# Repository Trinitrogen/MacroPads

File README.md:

# MacroPads
Repository for various Macropads

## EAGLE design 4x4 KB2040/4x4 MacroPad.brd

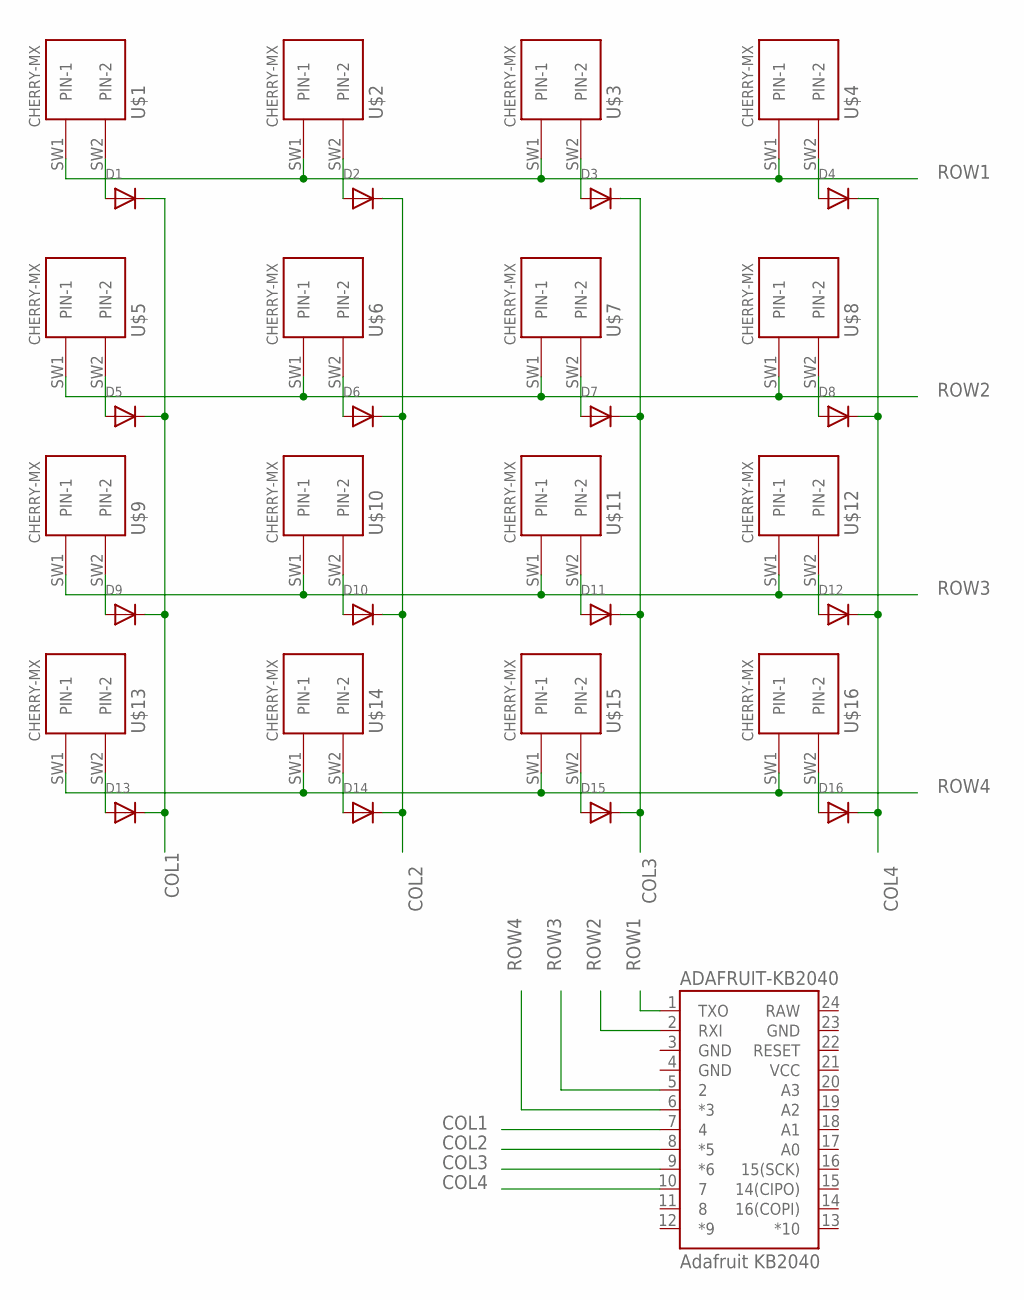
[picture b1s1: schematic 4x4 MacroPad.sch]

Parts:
ADAFRUIT-KB2040: Adafruit KB2040; SPARKFUN_PRO_MICRO
D1, D2, D3, D4, D5, D6, D7, D8, D9, D10, D11, D12, D13, D14, D15, D16: DIODESOD-123; SOD-123
U$1, U$2, U$3, U$4, U$5, U$6, U$7, U$8, U$9, U$10, U$11, U$12, U$13, U$14, U$15, U$16: CHERRY-MX

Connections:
C1: D1.A, U$1.SW2 (PIN-2)
C2: D2.A, U$2.SW2 (PIN-2)
C3: D3.A, U$3.SW2 (PIN-2)
C4: D4.A, U$4.SW2 (PIN-2)
COL1: ADAFRUIT-KB2040.7 (4), D1.C, D5.C, D9.C, D13.C
COL2: ADAFRUIT-KB2040.8 (*5), D2.C, D6.C, D10.C, D14.C
COL3: ADAFRUIT-KB2040.9 (*6), D3.C, D7.C, D11.C, D15.C
COL4: ADAFRUIT-KB2040.10 (7), D4.C, D8.C, D12.C, D16.C
GND: ADAFRUIT-KB2040.3 (GND), ADAFRUIT-KB2040.4 (GND), ADAFRUIT-KB2040.23 (GND)
unnamed: D5.A, U$5.SW2 (PIN-2)
unnamed: D6.A, U$6.SW2 (PIN-2)
unnamed: D7.A, U$7.SW2 (PIN-2)
unnamed: D8.A, U$8.SW2 (PIN-2)
unnamed: D9.A, U$9.SW2 (PIN-2)
unnamed: D10.A, U$10.SW2 (PIN-2)
unnamed: D11.A, U$11.SW2 (PIN-2)
unnamed: D12.A, U$12.SW2 (PIN-2)
unnamed: D13.A, U$13.SW2 (PIN-2)
unnamed: D14.A, U$14.SW2 (PIN-2)
unnamed: D15.A, U$15.SW2 (PIN-2)
unnamed: D16.A, U$16.SW2 (PIN-2)
RAW: ADAFRUIT-KB2040.24 (RAW)
ROW1: ADAFRUIT-KB2040.1 (TXO), U$1.SW1 (PIN-1), U$2.SW1 (PIN-1), U$3.SW1 (PIN-1), U$4.SW1 (PIN-1)
ROW2: ADAFRUIT-KB2040.2 (RXI), U$5.SW1 (PIN-1), U$6.SW1 (PIN-1), U$7.SW1 (PIN-1), U$8.SW1 (PIN-1)
ROW3: ADAFRUIT-KB2040.5 (2), U$9.SW1 (PIN-1), U$10.SW1 (PIN-1), U$11.SW1 (PIN-1), U$12.SW1 (PIN-1)
ROW4: ADAFRUIT-KB2040.6 (*3), U$13.SW1 (PIN-1), U$14.SW1 (PIN-1), U$15.SW1 (PIN-1), U$16.SW1 (PIN-1)
VCC: ADAFRUIT-KB2040.21 (VCC)

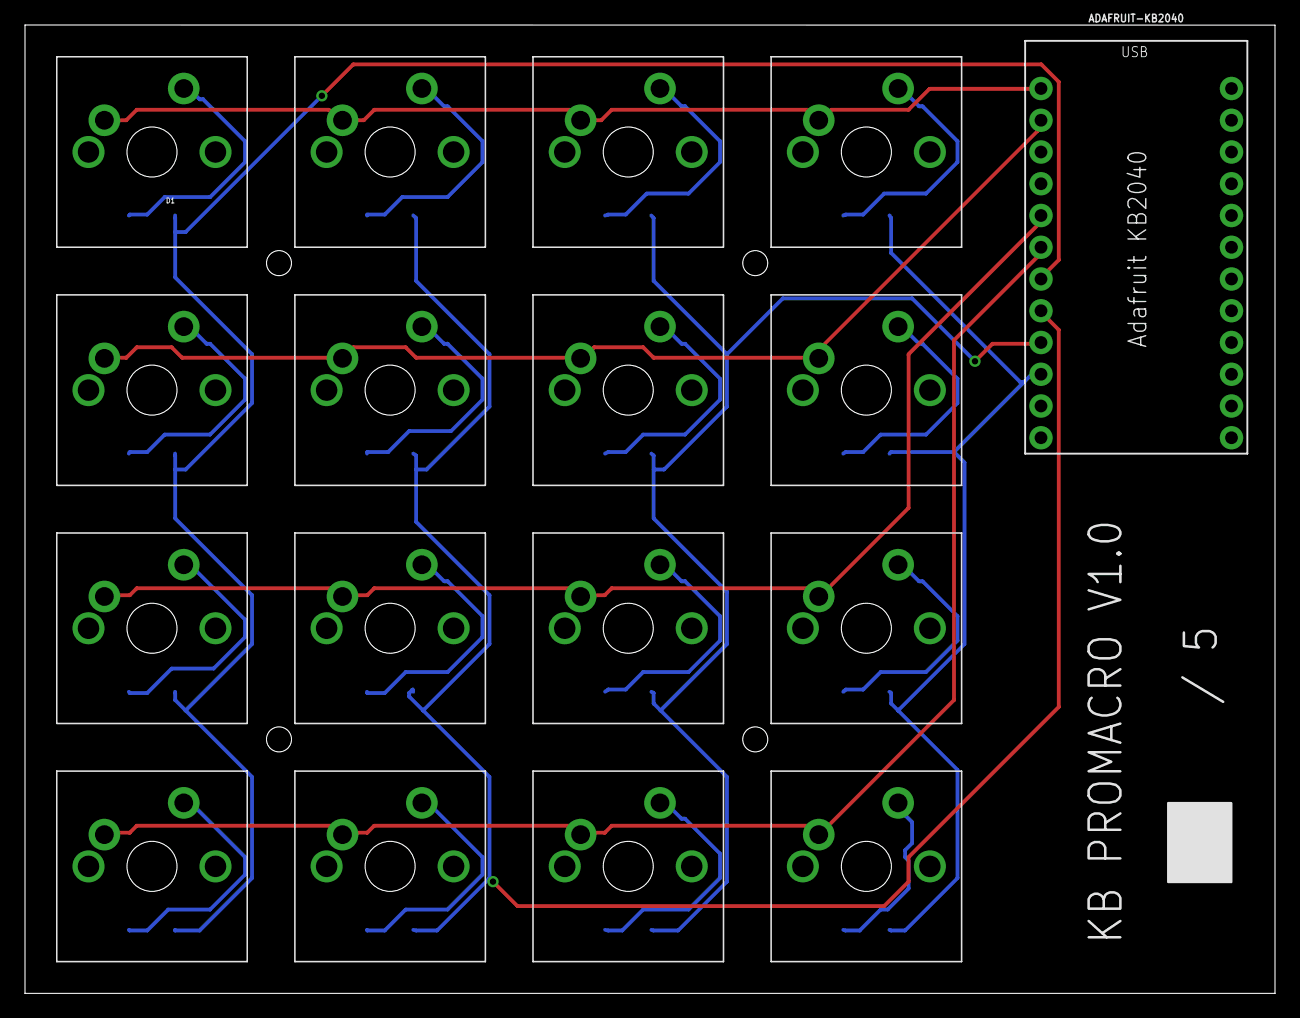
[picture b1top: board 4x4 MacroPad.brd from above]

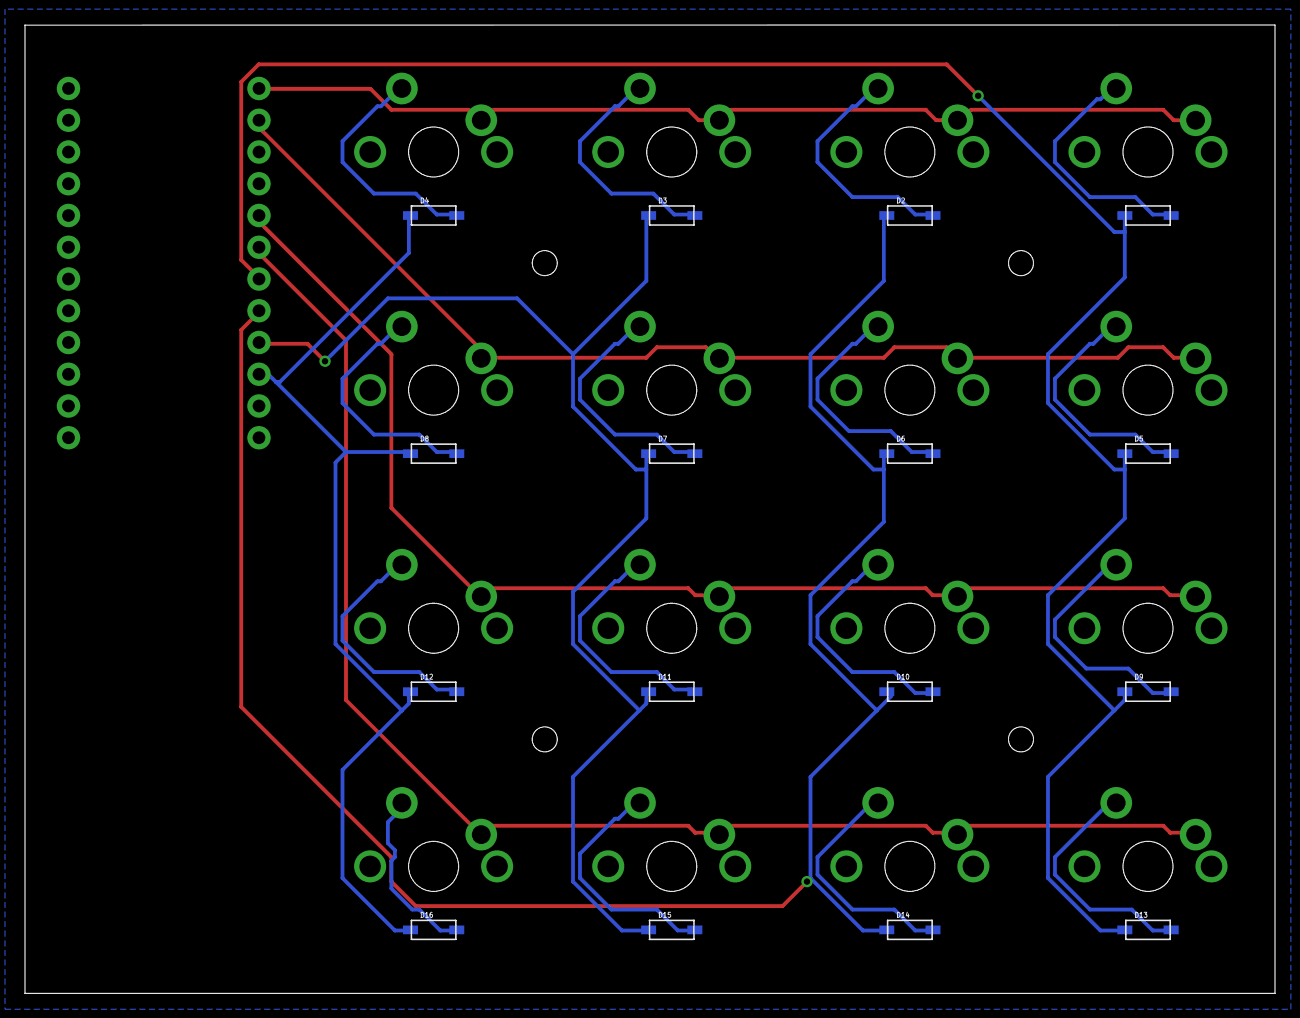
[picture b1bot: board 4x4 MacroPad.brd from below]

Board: 2 copper layers, 100.0 x 77.5 mm, 33 parts (16 on the bottom side), 25 nets.

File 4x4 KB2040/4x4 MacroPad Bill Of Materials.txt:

Partlist exported from C:/Users/kbell/OneDrive/Documents/EAGLE/projects/MacroPads/4x4 KB2040/4x4 MacroPad.sch at 3/24/2023 8:19 AM

Part            Value           Device             Package            Description                URL                                  
ADAFRUIT-KB2040 Adafruit KB2040 SPARKFUN_PRO_MICRO SPARKFUN_PRO_MICRO SparkFun Pro Micro         https://www.adafruit.com/product/5302
D1                              DIODESOD-123       SOD-123            Diode                      https://www.adafruit.com/product/5099
D2                              DIODESOD-123       SOD-123            Diode                      https://www.adafruit.com/product/5099
D3                              DIODESOD-123       SOD-123            Diode                      https://www.adafruit.com/product/5099
D4                              DIODESOD-123       SOD-123            Diode                      https://www.adafruit.com/product/5099
D5                              DIODESOD-123       SOD-123            Diode                      https://www.adafruit.com/product/5099
D6                              DIODESOD-123       SOD-123            Diode                      https://www.adafruit.com/product/5099
D7                              DIODESOD-123       SOD-123            Diode                      https://www.adafruit.com/product/5099
D8                              DIODESOD-123       SOD-123            Diode                      https://www.adafruit.com/product/5099
D9                              DIODESOD-123       SOD-123            Diode                      https://www.adafruit.com/product/5099
D10                             DIODESOD-123       SOD-123            Diode                      https://www.adafruit.com/product/5099
D11                             DIODESOD-123       SOD-123            Diode                      https://www.adafruit.com/product/5099
D12                             DIODESOD-123       SOD-123            Diode                      https://www.adafruit.com/product/5099
D13                             DIODESOD-123       SOD-123            Diode                      https://www.adafruit.com/product/5099
D14                             DIODESOD-123       SOD-123            Diode                      https://www.adafruit.com/product/5099
D15                             DIODESOD-123       SOD-123            Diode                      https://www.adafruit.com/product/5099
D16                             DIODESOD-123       SOD-123            Diode                      https://www.adafruit.com/product/5099
U$1             CHERRY-MX       CHERRY-MX          CHERRY-MX          Cherry MX series keyswitch https://www.adafruit.com/product/5122
U$2             CHERRY-MX       CHERRY-MX          CHERRY-MX          Cherry MX series keyswitch https://www.adafruit.com/product/5122
U$3             CHERRY-MX       CHERRY-MX          CHERRY-MX          Cherry MX series keyswitch https://www.adafruit.com/product/5122
U$4             CHERRY-MX       CHERRY-MX          CHERRY-MX          Cherry MX series keyswitch https://www.adafruit.com/product/5122
U$5             CHERRY-MX       CHERRY-MX          CHERRY-MX          Cherry MX series keyswitch https://www.adafruit.com/product/5122
U$6             CHERRY-MX       CHERRY-MX          CHERRY-MX          Cherry MX series keyswitch https://www.adafruit.com/product/5122
U$7             CHERRY-MX       CHERRY-MX          CHERRY-MX          Cherry MX series keyswitch https://www.adafruit.com/product/5122
U$8             CHERRY-MX       CHERRY-MX          CHERRY-MX          Cherry MX series keyswitch https://www.adafruit.com/product/5122
U$9             CHERRY-MX       CHERRY-MX          CHERRY-MX          Cherry MX series keyswitch https://www.adafruit.com/product/5122
U$10            CHERRY-MX       CHERRY-MX          CHERRY-MX          Cherry MX series keyswitch https://www.adafruit.com/product/5122
U$11            CHERRY-MX       CHERRY-MX          CHERRY-MX          Cherry MX series keyswitch https://www.adafruit.com/product/5122
U$12            CHERRY-MX       CHERRY-MX          CHERRY-MX          Cherry MX series keyswitch https://www.adafruit.com/product/5122
U$13            CHERRY-MX       CHERRY-MX          CHERRY-MX          Cherry MX series keyswitch https://www.adafruit.com/product/5122
U$14            CHERRY-MX       CHERRY-MX          CHERRY-MX          Cherry MX series keyswitch https://www.adafruit.com/product/5122
U$15            CHERRY-MX       CHERRY-MX          CHERRY-MX          Cherry MX series keyswitch https://www.adafruit.com/product/5122
U$16            CHERRY-MX       CHERRY-MX          CHERRY-MX          Cherry MX series keyswitch https://www.adafruit.com/product/5122

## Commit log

2023-03-24 Added Enclosure
2023-03-24 Added BOM
2023-03-24 Added Code.Py
2023-03-29 3x4 Initial Commit
2023-03-31 removal

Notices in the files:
parts and their libraries:
SparkFun-Boards: Licensing: Creative Commons ShareAlike 4.0 International - https://creativecommons.org/licenses/by-sa/4.0
